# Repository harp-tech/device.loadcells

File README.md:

## Harp Load Cells Interface and Reader

This pair of boards can be used to acquire analog signals from load cells and output their data to a USB host. It is additionally able to emit programmable digital events.

### Key Features ###

* Load cells interface
  * Controls up to 2 load cells readers
  * Digital outputs can be regulated at 3V or 5V
* Load Cells Reader
  * Up to 4 load cell sensors
  * 1kHz sampling rate
  * Load cells offset compensation

### Connectivity ###

* Load cells interface
  * 1x BNC input signal (IN0)
  * 1x BNC output signal (Out0)
  * 1x screw terminal connector interface (GND, DOUT1 to DOUT8, DIN0)
  * 2x RJ45 for digital inputs (from load cells devices)
  * 1x stereo jack for clock sync input (CLKIN)
  * 1x USB (for computer)
  * 1x power barrel connector jack (12V only)
  * 1x screw terminal connector for 5V output (GND, +5V)
* Load Cells Reader
  * 4x flick lock connectors (X1 to X4) with 4 analog inputs each (5V, I+, I-, 0V)
  * 1x digital output [RJ45]

## Interface ##

The interface with the Harp board can be done through [Bonsai](https://bonsai-rx.org/) or a dedicated GUI (Graphical User Interface).

In order to use this GUI, there are some software that needs to be installed:

1 - Install the [drivers](https://bitbucket.org/fchampalimaud/downloads/downloads/UsbDriver-2.12.26.zip).

2 - Install the [runtime](https://bitbucket.org/fchampalimaud/downloads/downloads/Runtime-1.0.zip).

3 - Reboot the computer.

4 - Install the [GUI](https://bitbucket.org/fchampalimaud/downloads/downloads/Harp%20Load%20Cells%20v1.1.0.zip).

## Licensing ##

Each subdirectory will contain a license or, possibly, a set of licenses if it involves both hardware and software.

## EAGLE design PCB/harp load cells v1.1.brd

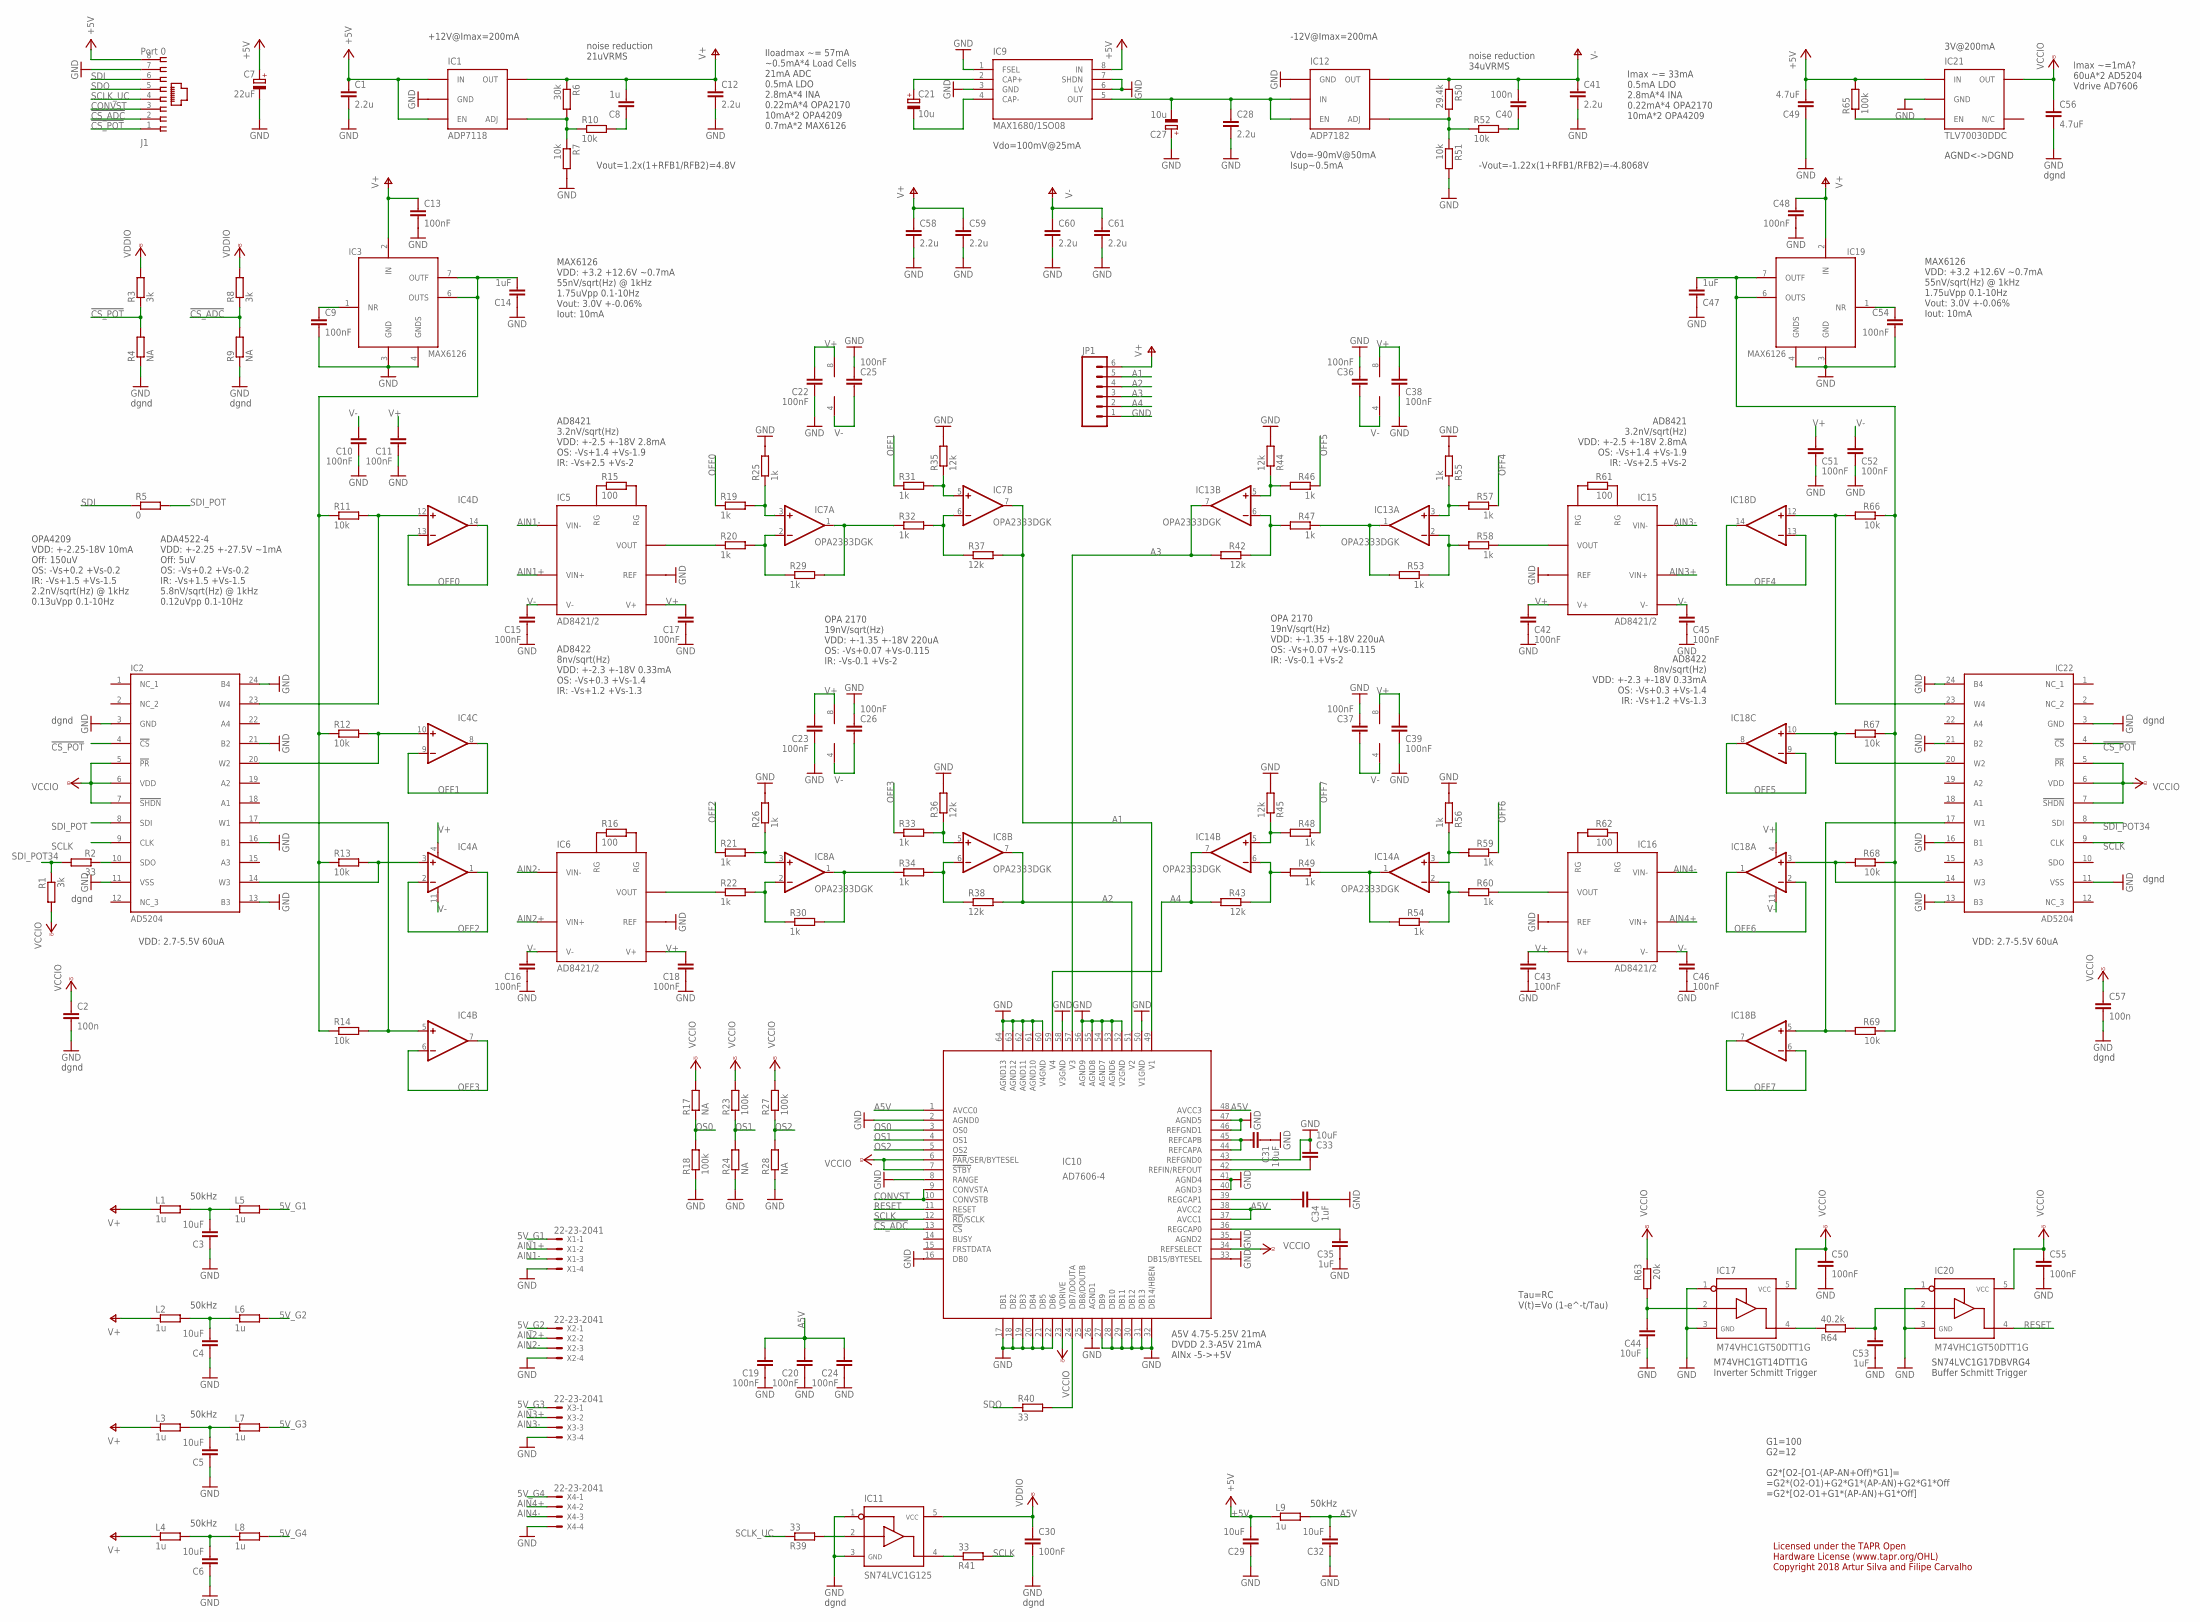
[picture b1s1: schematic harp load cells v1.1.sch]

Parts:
C1, C12, C28, C41, C58, C59, C60, C61: 2.2u; C0603
C2, C40, C57: 100n; C0402
C3, C4, C5, C6, C29, C31, C32, C33, C44: 10uF; C0603
C7: 22uF; CAP_100UF_HAND
C8: 1u; C0402
C9, C10, C11, C13, C15, C16, C17, C18, C19, C20, C22, C23, C24, C25, C26, C30, C36, C37, C38, C39, C42, C43, C45, C46, C48, C50, C51, C52, C54, C55: 100nF; C0402
C14, C47, C53: 1uF; C0603
C21, C27: 10u; A/3216-18W
C34, C35: 1uF; C0402
C49, C56: 4.7uF; C0603
IC1: ADP7118; TSOT23-5
IC2, IC22: AD5204; TSSOP-24
IC3, IC19: MAX6126; SO08
IC4, IC18: OPA4336T; TSSOP-14
IC5, IC6, IC15, IC16: AD8421/2; MSOP8
IC7, IC8, IC13, IC14: OPA2333DGK; MSOP08
IC9: MAX1680/1SO08; SO08
IC10: AD7606-4; LQFP-64
IC11: SN74LVC1G125; SOT23-5
IC12: ADP7182; TSOT23-5
IC17, IC20: M74VHC1GT50DTT1G; SOT23-5
IC21: TLV70030DDC; TSOT23-5
J1: Port 0; 520426-4
JP1: M06NO_SILK; 1X06_NO_SILK
L1, L2, L3, L4, L5, L6, L7, L8, L9: 1u; R0402
R1, R3, R8: 3k; R0402
R2, R39, R40, R41: 33; R0402
R4, R9, R17, R24, R28: NA; R0402
R5: 0; R0402
R6: 30k; R0402
R7, R10, R11, R12, R13, R14, R51, R52, R66, R67, R68, R69: 10k; R0402
R15, R16, R61, R62: 100; R0402
R18, R23, R27, R65: 100k; R0402
R19, R20, R21, R22, R25, R26, R29, R30, R31, R32, R33, R34, R46, R47, R48, R49, R53, R54, R55, R56, R57, R58, R59, R60: 1k; R0402
R35, R36, R37, R38, R42, R43, R44, R45: 12k; R0402
R50: 29.4k; R0402
R63: 20k; R0402
R64: 40.2k; R0402
X1, X2, X3, X4: 22-23-2041

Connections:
5V_G1: L5.2, X1.1
5V_G2: L6.2, X2.1
5V_G3: L7.2, X3.1
5V_G4: L8.2, X4.1
!CS_ADC: IC10.13 (!CS), J1.2, R8.1, R9.2
!CS_POT: IC2.4 (!CS), IC22.4 (!CS), J1.1, R3.1, R4.2
+5V: C1.1, C7.+, C29.2, C49.2, IC1.1 (IN), IC1.3 (EN), IC9.8 (IN), IC21.1 (IN), J1.8, L9.1, R65.2
A1: IC7.7 (OUT), IC10.49 (V1), JP1.5, R37.2
A2: IC8.7 (OUT), IC10.51 (V2), JP1.4, R38.2
A3: IC10.57 (V3), IC13.7 (OUT), JP1.3, R42.2
A4: IC10.59 (V4), IC14.7 (OUT), JP1.2, R43.2
A5V: C19.2, C20.2, C24.2, C32.2, IC10.1 (AVCC0), IC10.37 (AVCC1), IC10.38 (AVCC2), IC10.48 (AVCC3), L9.2
AIN1+: IC5.P$4 (VIN+), X1.2
AIN1-: IC5.P$1 (VIN-), X1.3
AIN2+: IC6.P$4 (VIN+), X2.2
AIN2-: IC6.P$1 (VIN-), X2.3
AIN3+: IC15.P$4 (VIN+), X3.2
AIN3-: IC15.P$1 (VIN-), X3.3
AIN4+: IC16.P$4 (VIN+), X4.2
AIN4-: IC16.P$1 (VIN-), X4.3
CONVST: IC10.9 (CONVSTA), IC10.10 (CONVSTB), J1.3
GND: C1.2, C2.2, C3.1, C4.1, C5.1, C6.1, C7.-, C9.2, C10.1, C11.1, C12.2, C13.2, C14.1, C15.1, C16.1, C17.1, C18.1, C19.1, C20.1, C22.1, C23.1, C24.1, C25.1, C26.1, C27.+, C28.2, C29.1, C30.2, C31.1, C32.1, C33.1, C34.1, C35.1, C36.1, C37.1, C38.1, C39.1, C41.2, C42.1, C43.1, C44.1, C45.1, C46.1, C47.1, C48.2, C49.1, C50.2, C51.1, C52.1, C53.1, C54.2, C55.2, C56.2, C57.2, C58.2, C59.2, C60.2, C61.2, IC1.2 (GND), IC2.3 (GND), IC2.11 (VSS), IC2.13 (B3), IC2.16 (B1), IC2.21 (B2), IC2.24 (B4), IC3.3 (GND), IC3.4 (GNDS), IC5.P$6 (REF), IC6.P$6 (REF), IC9.1 (FSEL), IC9.3 (GND), IC9.6 (LV), IC9.7 (SHDN), IC10.2 (AGND0), IC10.8 (RANGE), IC10.16 (DB0), IC10.17 (DB1), IC10.18 (DB2), IC10.19 (DB3), IC10.20 (DB4)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
unnamed: IC21.3 (EN), R65.1
unnamed: IC12.4 (ADJ), R50.2, R51.1, R52.1
unnamed: C44.2, IC17.2, R63.2
unnamed: C35.2, IC10.36 (REGCAP0)
unnamed: IC6.P$7 (VOUT), R22.1
unnamed: C40.1, R52.2
unnamed: C6.2, L4.2, L8.1
unnamed: IC17.4, R64.1
unnamed: C21.+, IC9.2 (CAP+)
unnamed: C21.-, IC9.4 (CAP-)
unnamed: C27.-, C28.1, IC9.5 (OUT), IC12.2 (IN), IC12.3 (EN)
unnamed: C53.2, IC20.2, R64.2
unnamed: IC7.6 (-IN), R32.2, R37.1
unnamed: C34.2, IC10.39 (REGCAP1)
unnamed: IC13.2 (-IN), R53.1, R58.2
unnamed: IC7.2 (-IN), R20.2, R29.1
unnamed: IC7.3 (+IN), R19.2, R25.1
unnamed: IC7.5 (+IN), R31.2, R35.1
unnamed: C33.2, IC10.42 (REFIN/REFOUT)
unnamed: IC13.3 (+IN), R55.1, R57.2
unnamed: IC13.6 (-IN), R42.1, R47.2
unnamed: IC13.5 (+IN), R44.1, R46.2
unnamed: C31.2, IC10.44 (REFCAPA), IC10.45 (REFCAPB)
unnamed: C8.1, R10.2
unnamed: IC1.4 (ADJ), R6.2, R7.1, R10.1
unnamed: IC5.P$2 (RG), R15.2
unnamed: IC5.P$3 (RG), R15.1
unnamed: IC5.P$7 (VOUT), R20.1
unnamed: IC8.2 (-IN), R22.2, R30.1
unnamed: IC6.P$2 (RG), R16.2
unnamed: IC6.P$3 (RG), R16.1
unnamed: IC8.3 (+IN), R21.2, R26.1
unnamed: IC7.1 (OUT), R29.2, R32.1
unnamed: IC8.6 (-IN), R34.2, R38.1
unnamed: C9.1, IC3.1 (NR)
unnamed: IC8.5 (+IN), R33.2, R36.1
unnamed: IC15.P$2 (RG), R61.2
unnamed: IC8.1 (OUT), R30.2, R34.1
unnamed: IC15.P$3 (RG), R61.1
unnamed: IC15.P$7 (VOUT), R58.1
unnamed: IC2.20 (W2), IC4.10 (+IN), R12.2
unnamed: IC16.P$2 (RG), R62.2
unnamed: IC2.17 (W1), IC4.5 (+IN), R14.2
unnamed: IC16.P$3 (RG), R62.1
unnamed: C14.2, IC3.6 (OUTS), IC3.7 (OUTF), R11.1, R12.1, R13.1, R14.1
unnamed: IC18.10 (+IN), IC22.20 (W2), R67.2
unnamed: IC18.12 (+IN), IC22.23 (W4), R66.2
unnamed: IC11.2, R39.2
unnamed: IC2.10 (SDO), R2.1
unnamed: C5.2, L3.2, L7.1
unnamed: IC18.3 (+IN), IC22.14 (W3), R68.2
unnamed: IC18.5 (+IN), IC22.17 (W1), R69.2
unnamed: IC13.1 (OUT), R47.1, R53.2
unnamed: C54.1, IC19.1 (NR)
unnamed: C47.2, IC19.6 (OUTS), IC19.7 (OUTF), R66.1, R67.1, R68.1, R69.1
unnamed: IC2.14 (W3), IC4.3 (+IN), R13.2
unnamed: IC14.2 (-IN), R54.1, R60.2
unnamed: IC14.3 (+IN), R56.1, R59.2
unnamed: IC14.6 (-IN), R43.1, R49.2
unnamed: IC14.5 (+IN), R45.1, R48.2
unnamed: IC2.23 (W4), IC4.12 (+IN), R11.2
unnamed: IC11.4, R41.1
unnamed: IC14.1 (OUT), R49.1, R54.2
unnamed: IC16.P$7 (VOUT), R60.1
unnamed: C4.2, L2.2, L6.1
unnamed: C3.2, L1.2, L5.1
unnamed: IC10.24 (DB7/DOUTA), R40.2
OFF0: IC4.13 (-IN), IC4.14 (OUT), R19.1
OFF1: IC4.8 (OUT), IC4.9 (-IN), R31.1
OFF2: IC4.1 (OUT), IC4.2 (-IN), R21.1
OFF3: IC4.6 (-IN), IC4.7 (OUT), R33.1
OFF4: IC18.13 (-IN), IC18.14 (OUT), R57.1
OFF5: IC18.8 (OUT), IC18.9 (-IN), R46.1
OFF6: IC18.1 (OUT), IC18.2 (-IN), R59.1
OFF7: IC18.6 (-IN), IC18.7 (OUT), R48.1
OS0: IC10.3 (OS0), R17.1, R18.2
OS1: IC10.4 (OS1), R23.1, R24.2
OS2: IC10.5 (OS2), R27.1, R28.2
RESET: IC10.11 (RESET), IC20.4
SCLK: IC2.9 (CLK), IC10.12 (!RD!/SCLK), IC22.9 (CLK), R41.2
SCLK_UC: J1.4, R39.1
SDI: J1.6, R5.1
SDI_POT: IC2.8 (SDI), R5.2
SDI_POT34: IC22.8 (SDI), R1.1, R2.2
SDO: J1.5, R40.1
V+: C8.2, C11.2, C12.1, C13.1, C17.2, C18.2, C22.2, C23.2, C38.2, C39.2, C42.2, C43.2, C48.1, C51.2, C58.1, C59.1, IC1.5 (OUT), IC3.2 (IN), IC4.4 (V+), IC5.P$8 (V+), IC6.P$8 (V+), IC7.8 (V+), IC8.8 (V+), IC13.8 (V+), IC14.8 (V+), IC15.P$8 (V+), IC16.P$8 (V+), IC18.4 (V+), IC19.2 (IN), JP1.6, L1.1, L2.1, L3.1, L4.1, R6.1
V-: C10.2, C15.2, C16.2, C25.2, C26.2, C36.2, C37.2, C40.2, C41.1, C45.2, C46.2, C52.2, C60.1, C61.1, IC4.11 (V-), IC5.P$5 (V-), IC6.P$5 (V-), IC7.4 (V-), IC8.4 (V-), IC12.5 (OUT), IC13.4 (V-), IC14.4 (V-), IC15.P$5 (V-), IC16.P$5 (V-), IC18.11 (V-), R50.1
VCCIO: C2.1, C30.1, C50.1, C55.1, C56.1, C57.1, IC2.5 (!PR), IC2.6 (VDD), IC2.7 (!SHDN), IC10.6 (!PAR!/SER/BYTESEL), IC10.7 (!STBY), IC10.23 (VDRIVE), IC10.34 (REFSELECT), IC11.5, IC17.5, IC20.5, IC21.5 (OUT), IC22.5 (!PR), IC22.6 (VDD), IC22.7 (!SHDN), R1.2, R3.2, R8.2, R17.2, R23.2, R27.2, R63.1

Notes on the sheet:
A5V 4.75-5.25V 21mA DVDD 2.3-A5V 21mA AINx -5->+5V
AD8421 3.2nV/sqrt(Hz) VDD: +-2.5 +-18V 2.8mA OS: -Vs+1.4 +Vs-1.9 IR: -Vs+2.5 +Vs-2
VDD: 2.7-5.5V 60uA
3V@200mA
50kHz
Licensed under the TAPR Open Hardware License (www.tapr.org/OHL) Copyright 2018 Artur Silva and Filipe Carvalho
Imax ~=1mA? 60uA*2 AD5204 Vdrive AD7606
AGND<->DGND
M74VHC1GT14DTT1G Inverter Schmitt Trigger
SN74LVC1G17DBVRG4 Buffer Schmitt Trigger
Tau=RC V(t)=Vo (1-e^-t/Tau)
dgnd
noise reduction 34uVRMS
-12V@Imax=200mA
-Vout=-1.22x(1+RFB1/RFB2)=-4.8068V
+12V@Imax=200mA
Vout=1.2x(1+RFB1/RFB2)=4.8V
noise reduction 21uVRMS
OPA4209 VDD: +-2.25-18V 10mA Off: 150uV OS: -Vs+0.2 +Vs-0.2 IR: -Vs+1.5 +Vs-1.5 2.2nV/sqrt(Hz) @ 1kHz 0.13uVpp 0.1-10Hz
Vdo=100mV@25mA
Vdo=-90mV@50mA Isup~0.5mA
AD8422 8nv/sqrt(Hz) VDD: +-2.3 +-18V 0.33mA OS: -Vs+0.3 +Vs-1.4 IR: -Vs+1.2 +Vs-1.3
Imax ~= 33mA 0.5mA LDO 2.8mA*4 INA 0.22mA*4 OPA2170 10mA*2 OPA4209
OPA 2170 19nV/sqrt(Hz) VDD: +-1.35 +-18V 220uA OS: -Vs+0.07 +Vs-0.115 IR: -Vs-0.1 +Vs-2
ADA4522-4 VDD: +-2.25 +-27.5V ~1mA Off: 5uV OS: -Vs+0.2 +Vs-0.2 IR: -Vs+1.5 +Vs-1.5 5.8nV/sqrt(Hz) @ 1kHz 0.12uVpp 0.1-10Hz
MAX6126 VDD: +3.2 +12.6V ~0.7mA 55nV/sqrt(Hz) @ 1kHz 1.75uVpp 0.1-10Hz Vout: 3.0V +-0.06% Iout: 10mA
Iloadmax ~= 57mA ~0.5mA*4 Load Cells 21mA ADC 0.5mA LDO 2.8mA*4 INA 0.22mA*4 OPA2170 10mA*2 OPA4209 0.7mA*2 MAX6126
G1=100 G2=12 G2*[O2-[O1-(AP-AN+Off)*G1]= =G2*(O2-O1)+G2*G1*(AP-AN)+G2*G1*Off =G2*[O2-O1+G1*(AP-AN)+G1*Off]

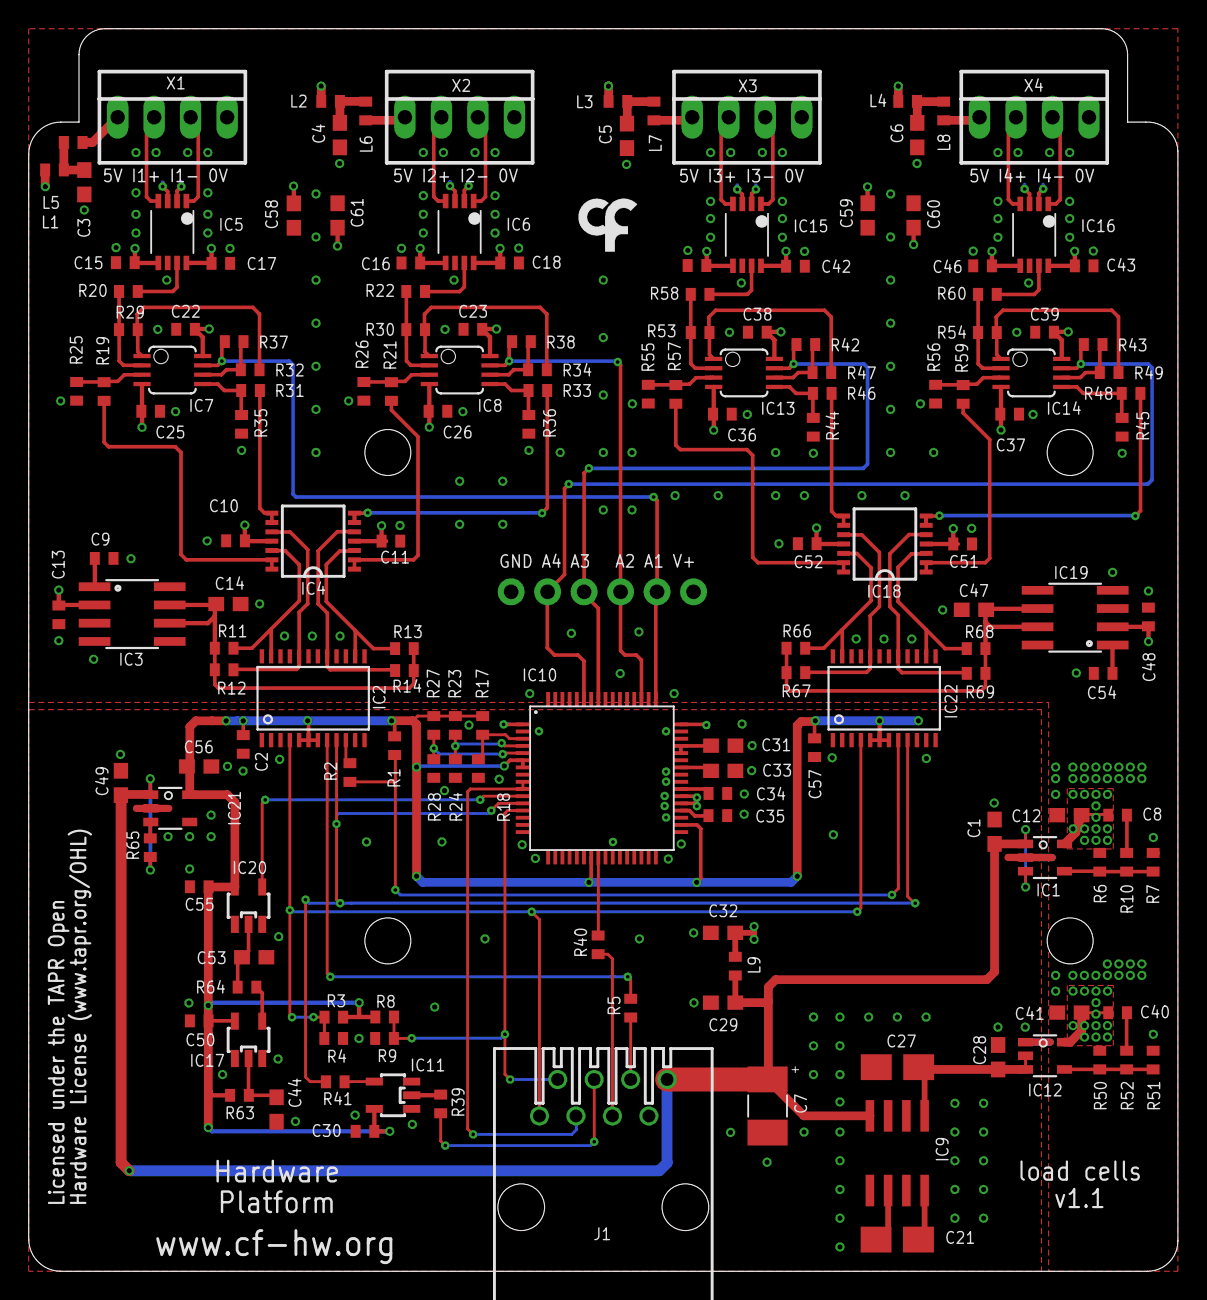
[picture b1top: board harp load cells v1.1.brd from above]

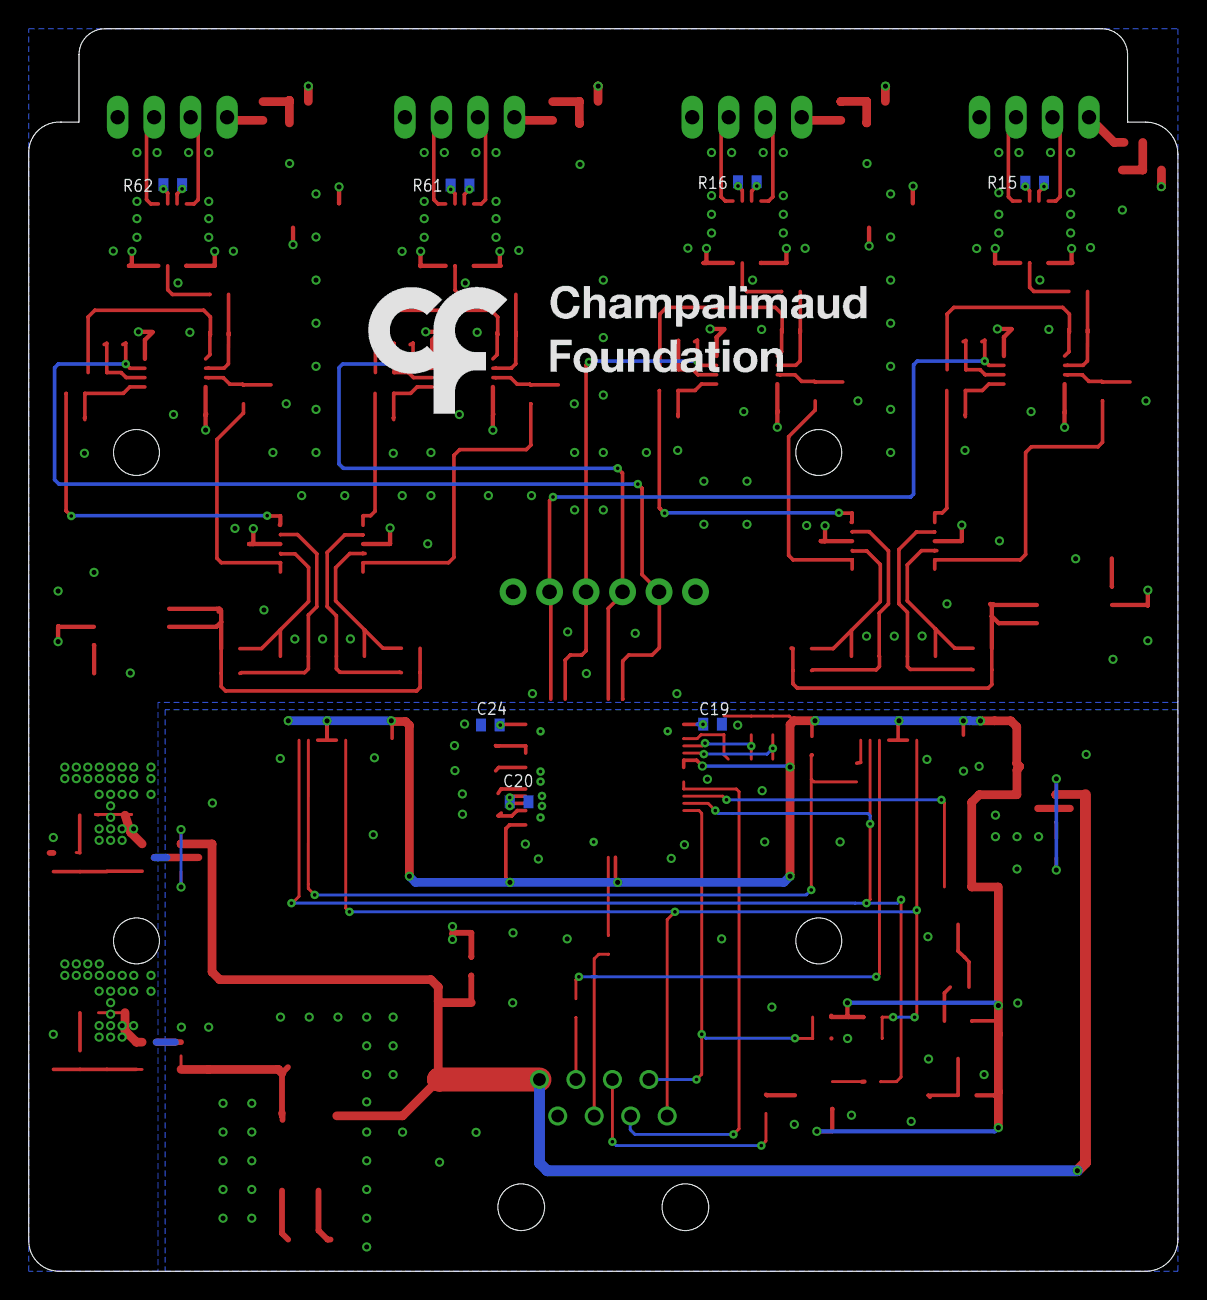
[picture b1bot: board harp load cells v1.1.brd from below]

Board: 4 copper layers, 80.0 x 86.5 mm, 169 parts (8 on the bottom side), 110 nets.

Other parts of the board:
U$1: LOGO_5
U$4: LOGO_7

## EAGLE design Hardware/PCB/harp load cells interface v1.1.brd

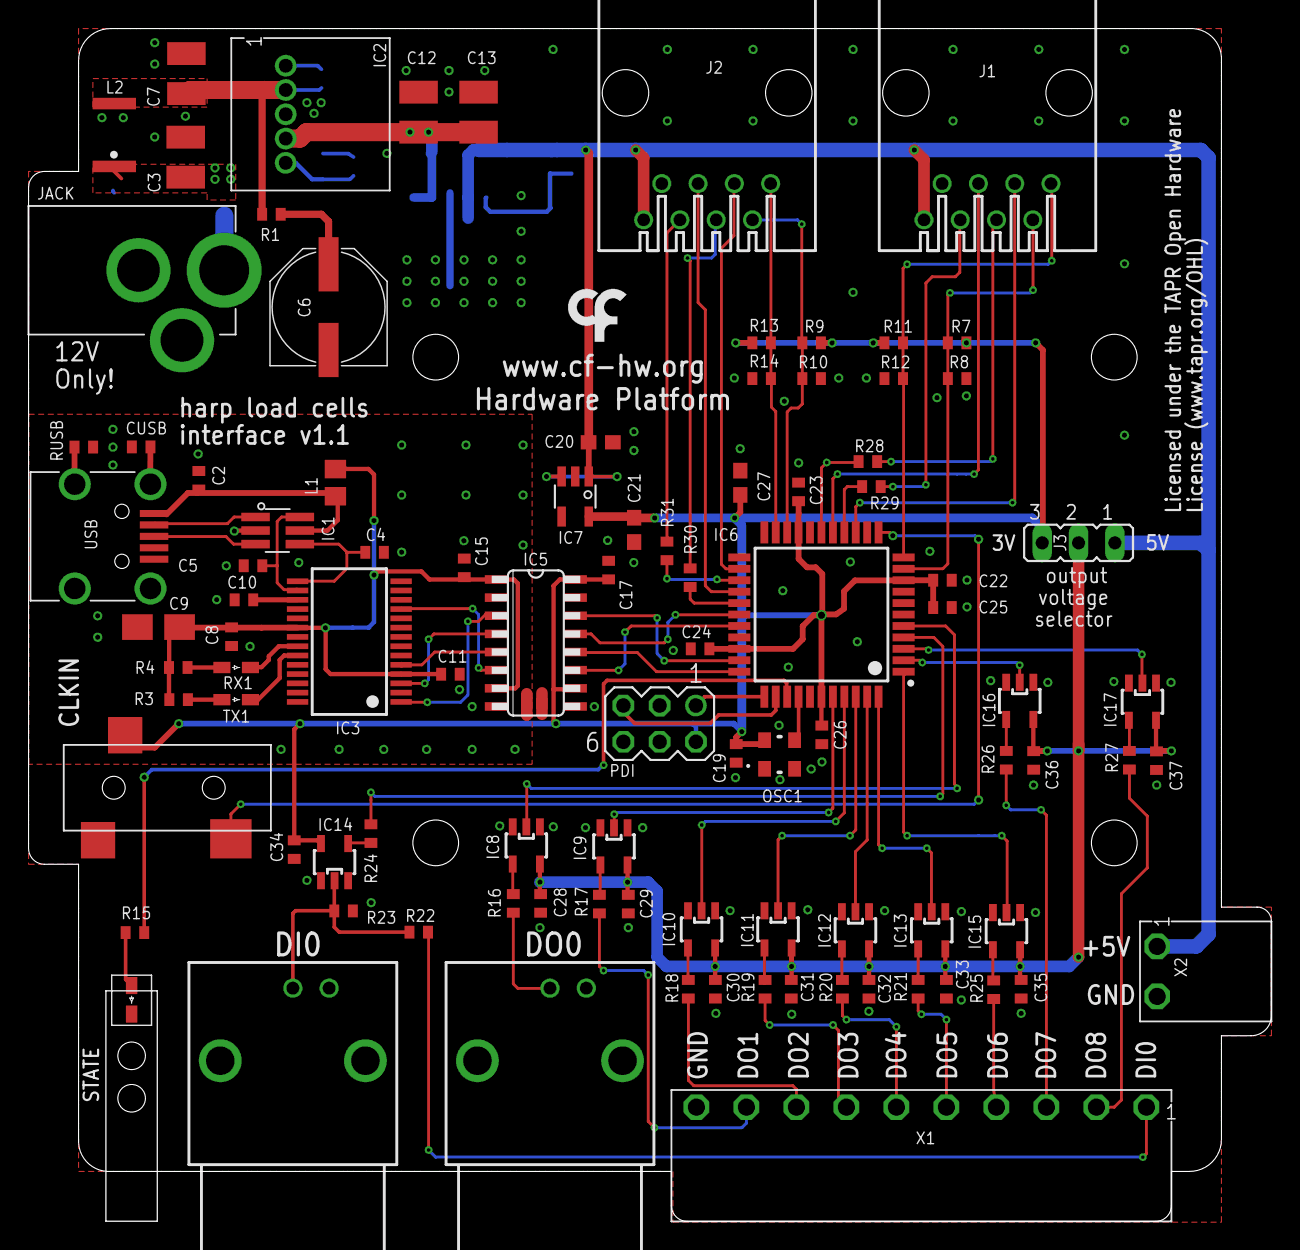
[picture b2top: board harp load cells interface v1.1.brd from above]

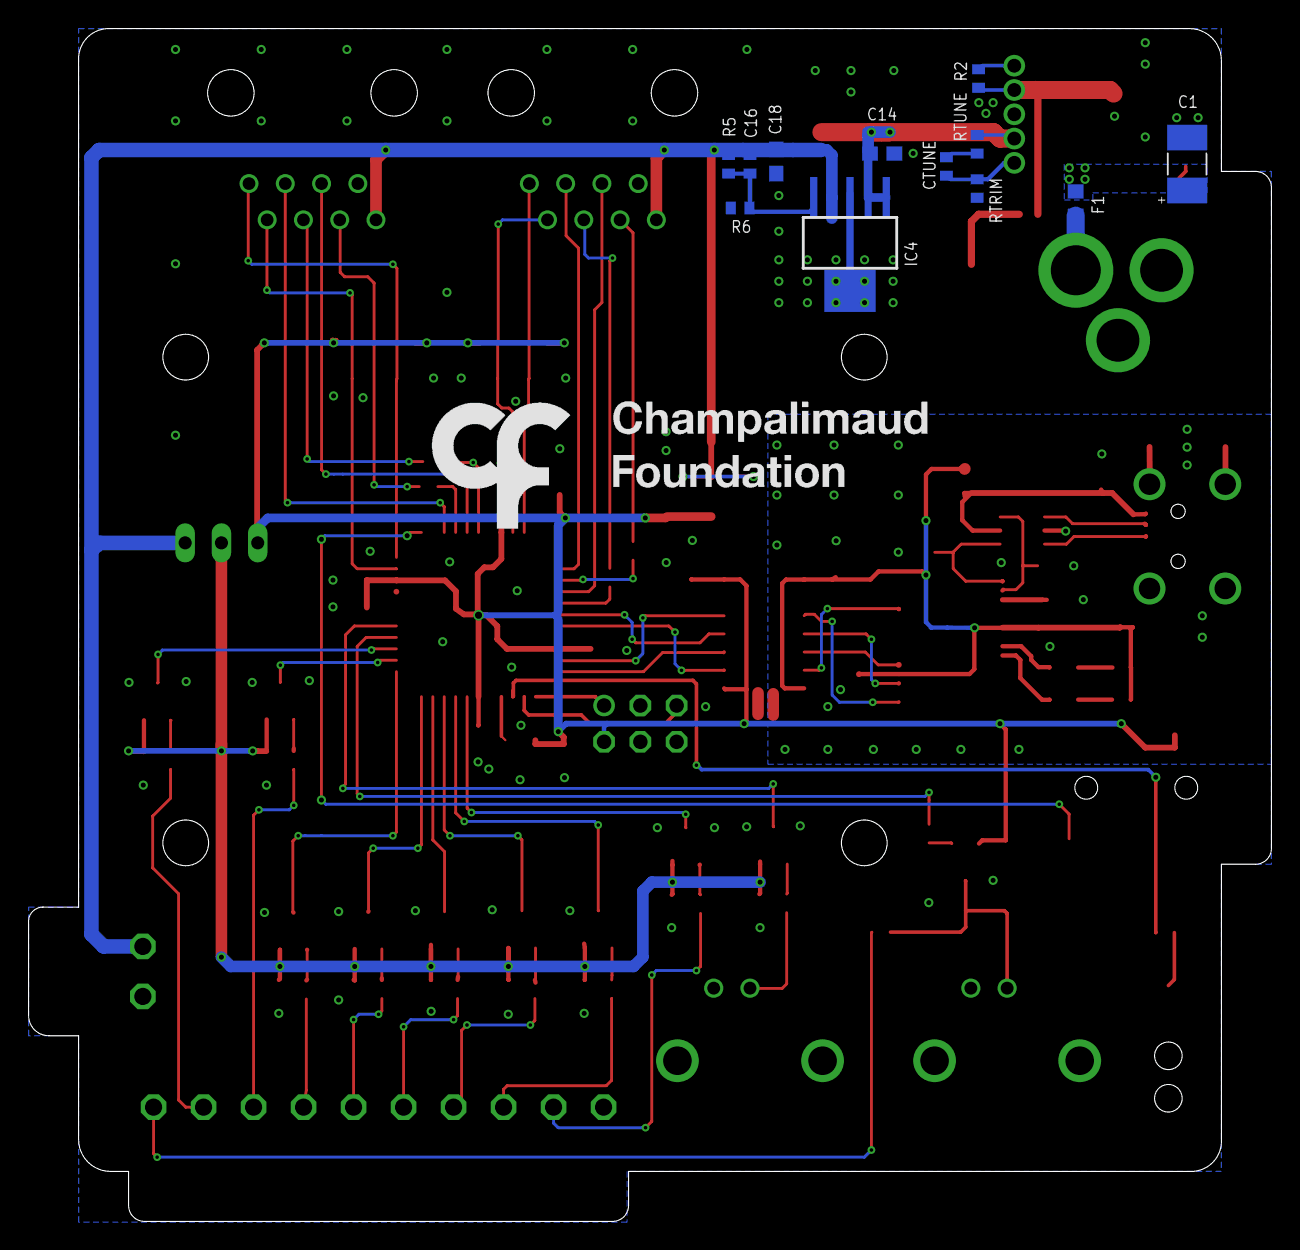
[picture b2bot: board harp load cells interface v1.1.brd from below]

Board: 2 copper layers, 87.0 x 83.5 mm, 113 parts (13 on the bottom side), 88 nets.

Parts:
C1: 22uF; CAP_100UF_HAND
C2, C8, C10, C11, C15, C17, C19, C22, C23, C24, C28, C29, C30, C31, C32, C33, C34, C35, C36, C37: 100nF; C0402
C3, C7: 22uF; C1210
C4, C5: 47pF; C0402
C6: 100uF; PANASONIC_E
C9: 4.7uF; A/3216-18W
C12, C13: 47uF; C1210
C14, C18, C20, C21, C27: 10uF; C0603
C16: 13pF; C0402
C25, C26: 330nF; C0402
CLKIN: 35RASMT2BHNTRX
CTUNE: NA; C0402
CUSB: 4.7nF; C0402
F1: 1A FB; R0603
IC1: USBLC6-2SC6; SOT23-6L
IC2: DC-DC-SIP-5; SIP-5
IC3: FT232RL; SSOP28
IC4: TPS78630DCQ; SOT223-6
IC5: SI8642BC-B-IS1; NSOIC-16
IC6: ATXMEGA128A4U-AU; QFP80P1200X1200X120-44N
IC7: LP5907MFX-3.3; TSOT23-5
IC8, IC9, IC10, IC11, IC12, IC13, IC14, IC15, IC16, IC17: SN74LVC1G125; SOT23-5
IN0: BNC; BNC_RA
J1, J2: Port 0; 520426-4
J3: JP2
JACK: DC_JACK2.1MM; DC_POWER_INPUT_2.1MM
L1: ???; R0805
L2: 1.5u; IND_LPS4012
OSC1: OSCILLATOR_3.2X2.5
OUT0: BNC; BNC_RA
PDI: MA03-2
R1: 0; R0402
R2, R7, R9, R11, R13: NA; R0402
R3: 2050 NA; R0402
R4: 680 NA; R0402
R5: 95.3k; R0402
R6: 30.9k; R0402
R8, R10, R12, R14, R23: 100k; R0402
R15: 68; R0402
R16, R17, R18, R19, R20, R21, R24, R25, R26, R27, R28, R29, R30, R31: 33; R0402
R22: 330; R0402
RTRIM: 243; R0402
RTUNE: NA; R0402
RUSB: 1M; R0402
RX1: GREEN NA; LED_HAND
STATE: GREEN; LED_HAND
TP1, TP2: TPTP08SQ; TP08SQ
TX1: RED NA; LED_HAND
U$1: LED_PIPE_7513D2-L
U$2: LOGO_5
U$4: LOGO_7
USB: 240-0002-1
X1: CON_3.5MM_1X10
X2: CON_3.5MM_1X2

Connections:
3V3OUT: C10.1, IC3.17
!CS0_0: IC6.14, J1.3
!CS0_1: IC6.10, J1.2, R7.1, R8.2
!CS0_2: IC6.11, J1.1, R11.1, R12.2
!CS1_0: IC6.24, J2.3
!CS1_1: IC6.20, J2.2, R9.1, R10.2
!CS1_2: IC6.21, J2.1, R13.1, R14.2
+5V: C16.1, C18.1, C20.1, IC4.P$4, IC7.1, IC7.3, J1.8, J2.8, J3.1, R5.2, X2.P1
+12V: C1.+, C3.1, F1.1, L2.1
+V: C28.1, C29.1, C30.1, C31.1, C32.1, C33.1, C35.1, C36.1, C37.1, IC8.5, IC9.5, IC10.5, IC11.5, IC12.5, IC13.5, IC15.5, IC16.5, IC17.5, J3.2
BNC_DI0: IC14.2, IN0.1, R22.2, R23.2
CLK_SYNC: CLKIN.4, IC6.12
CTS: IC5.11, IC6.29
DCIN: C7.1, IC2.P2, L2.2, R1.2, R2.2
DI0: R22.1, X1.P1
DO0: OUT0.1, R16.2
DO1: R17.2, X1.P9
DO2: R18.2, X1.P8
DO3: R19.2, X1.P7
DO4: R20.2, X1.P6
DO5: R21.2, X1.P5
DO6: R25.2, X1.P4
DO7: R26.2, X1.P3
DO8: R27.2, X1.P2
FT_CTS: IC3.11, IC5.6
FT_RTS: IC3.3, IC5.4
FT_RXD: IC3.5, IC5.5
FT_TXD: IC3.1, IC5.3
GND: C1.-, C3.2, C6.-, C7.2, C12.2, C13.2, C14.2, C17.2, C18.2, C19.2, C20.2, C21.2, C22.2, C23.2, C24.2, C25.2, C26.2, C27.2, C28.2, C29.2, C30.2, C31.2, C32.2, C33.2, C34.2, C35.2, C36.2, C37.2, CLKIN.5, IC2.P3, IC4.P$3, IC4.P$6, IC5.9, IC5.15, IC6.8, IC6.18, IC6.30, IC6.38, IC7.2, IC8.1, IC8.3, IC9.1, IC9.3, IC10.1, IC10.3, IC11.1, IC11.3, IC12.1, IC12.3, IC13.1, IC13.3, IC14.1, IC14.3, IC15.1, IC15.3, IC16.1, IC16.3, IC17.1, IC17.3, IN0.2, J1.7, J2.7, JACK.P2, JACK.P3, OSC1.P$2, OUT0.2, PDI.6, R6.1, R8.1, R10.1, R12.1, R14.1, R23.1, RTRIM.1, STATE.K, TP2.TP, X1.P10, X2.P2
GND2: C2.2, C4.2, C5.2, C8.2, C9.-, C10.2, C11.2, C15.2, CUSB.2, IC1.P$2, IC3.7, IC3.18, IC3.21, IC3.25, IC3.26, IC5.2, IC5.8, RUSB.2, TP1.TP, USB.P$5
IN00: IC6.4, R24.2
MISO0: IC6.16, J1.5
MISO1: IC6.26, J2.5
MOSI0: IC6.15, R29.1
MOSI0_T: J1.6, R29.2
MOSI1: IC6.25, R31.2
MOSI1_T: J2.6, R31.1
unnamed: IC16.4, R26.1
unnamed: IC15.4, R25.1
unnamed: IC10.4, R18.1
unnamed: R4.1, RX1.A
unnamed: IC17.4, R27.1
unnamed: IC3.22, RX1.K
unnamed: IC9.4, R17.1
unnamed: IC12.4, R20.1
unnamed: IC8.4, R16.1
unnamed: CTUNE.2, IC2.P5, RTRIM.2
unnamed: IC1.P$3, USB.P$3
unnamed: CTUNE.1, RTUNE.1
unnamed: CUSB.1, USB.SHIELD_4
unnamed: IC2.P1, R2.1
unnamed: IC13.4, R21.1
unnamed: F1.2, JACK.P1
unnamed: IC11.4, R19.1
unnamed: C16.2, IC4.P$5, R5.1, R6.2
unnamed: IC14.4, R24.1
unnamed: R15.1, STATE.A
unnamed: C6.+, R1.1
unnamed: C2.1, IC1.P$5, L1.2, USB.P$1
unnamed: R3.1, TX1.A
unnamed: IC3.23, TX1.K
unnamed: RUSB.1, USB.SHIELD_1
unnamed: IC1.P$1, USB.P$2
OSC1: IC6.37, OSC1.P$3
OUT00: IC6.5, IC8.2
OUT01: IC6.40, IC9.2
OUT02: IC6.41, IC10.2
OUT03: IC6.42, IC11.2
OUT04: IC6.43, IC12.2
OUT05: IC6.44, IC13.2
OUT06: IC6.1, IC15.2
OUT07: IC6.2, IC16.2
OUT08: IC6.3, IC17.2
P5.45V: C12.1, C13.1, C14.1, IC2.P4, IC4.P$1, IC4.P$2, RTUNE.2
PDI-CLK: IC6.35, PDI.5
PDI-DATA: IC6.34, PDI.1
RTS: IC5.13, IC6.28
RXD: IC5.12, IC6.33
SCK0: IC6.17, R28.1
SCK0_T: J1.4, R28.2
SCK1: IC6.27, R30.2
SCK1_T: J2.4, R30.1
STATE: IC6.36, R15.2
TXD: IC5.14, IC6.32
USB5V: C8.1, C9.+, C11.1, C15.1, IC3.4, IC3.20, IC5.1, IC5.7, L1.1, R3.2, R4.2
USBDM: C5.1, IC1.P$6, IC3.16
USBDP: C4.1, IC1.P$4, IC3.15
VCCIO: C17.1, C19.1, C21.1, C22.1, C23.1, C24.1, C25.1, C26.1, C27.1, C34.1, CLKIN.1, IC5.10, IC5.16, IC6.9, IC6.19, IC6.31, IC6.39, IC7.5, IC14.5, J3.3, OSC1.P$4, PDI.2, R7.2, R9.2, R11.2, R13.2

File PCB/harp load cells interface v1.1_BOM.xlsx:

| Part(s) | Quantity | Description | Distributor | Part. No.
 | IC1 | 1 | ESD Protection Low Cap | Mouser | 511-USBLC6-2SC6Y
 | IC2 | 1 | Conversores CC/CC sem isolação 12Vin, 0.591-6Vout 1.5A, Positive Logic | Mouser | 580-OKR-T/1.5-W12-C
 | IC3 | 1 | IC USB USB to Serial UART Enhanced IC SSOP-28 | Mouser | 895-FT232RL
 | IC4 | 1 | Reguladores de tensão de LDO High PSRR Fast RF High-Enable 1.5A | Mouser | 595-TPS78601DCQR
 | IC5 | 1 | Isoladores digitais Quad Ch 3.75V Iso 150M 2/2 NB, DO=LO | Mouser | 634-SI8642BC-B-IS1
 | IC6 | 1 | Microcontroladores de 8 bits - MCU 44TQFP, IND TEMP GREEN, 1.6-3.6V | Mouser | 556-ATXMEGA128A4U-AU
 | IC7 | 1 | LDO 250mA Ultra-Lo Noise LDO Reg | Mouser | 595-LP5907MFX-3.3NPB
 | IC8, IC9, IC10, IC11, IC12, IC13, IC14, IC15, IC16, IC17 | 10 | M74VHC1GT50DTT1G Buffer, Non-Inverting, 1.65V to 5.5V, SOT-23-5 | Mouser | 863-M74VHC1GT50DTT1G
 | C16 | 1 | CAP CER 13pF 50V ±5% C0G 0402 | Mouser | 81-GRM1555C1H130JA1D
 | C4, C5 | 2 | CAP CER 47pF 50V ±5% C0G 0402 | Mouser | 77-VJ0402A470JXACBC
 | CUSB | 1 | CAP CER 4.7nF 100V ±10% X7R 0402 | Mouser | 81-GRM155R72A472KA01
 | C2, C8, C10, C11, C15, C17, C19, C22, C23, C24, C25, C28, C29, C30, C31, C32, C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 | 21 | CAP CER 100nF 10V X5R 0402 | REEL | REEL
 | C26 | 1 | CAP CER 0.33uF 10V ±10% X5R 0402 | Mouser | GRM155R61A334KE15D
 | C9 | 1 | CAP TAN 4.7uF 6.3V ±10% 1206 | Mouser | 80-T491A475K006
 | C14, C18, C20, C21, C27 | 5 | CAP CER 10uF 10V ±10% X5R 0603 | Mouser | 81-GRM188R61A106KE9D
 | C1 | 1 | CAP TAN 22uF 20V ±10% 1210 | Mouser | 667-20TQC22MYFB
 | C3, C7 | 2 | CAP CER 22uF 25V ±10% X5R 1210 | Mouser | 81-GRM32ER61E226KE15
 | C12, C13 | 2 | CAP CER 47uF 10V ±10% X5R 1210 | Mouser | 81-GRM32ER61A476KE20
 | C6 | 1 | CAP ELE 100uF 25V ±20% | Mouser | 667-EEE-FK1E101P
 | R1 | 1 | RES SMD 0Ω OHM 5% 0402 | Mouser | 667-ERJ-2GE0R00X
 | R16, R17, R18, R19, R20, R21, R24, R25, R26, R27, R28, R29, R30, R31 | 14 | RES SMD 0402 33Ω, ± 1% | Mouser | 71-CRCW0402-33-E3
 | R15 | 1 | RES SMD 68Ω OHM 5% 0402 | Mouser | 71-CRCW0402-68-E3
 | RTRIM | 1 | RES SMD 243Ω OHM 1% 0402 | Mouser | 667-ERJ-2RKF2430X
 | R22 | 1 | RES SMD 330Ω OHM 1% 0402 | Mouser | 667-ERJ-PA2F3300X
 | R6 | 1 | RES SMD 30.9kΩ 1% 0402 | Mouser | 71-CRCW0402-30.9K-E3
 | R5 | 1 | RES SMD 95.3kΩ 1% 0402 | Mouser | 667-ERJ-2RKF9532X
 | R8, R10, R12, R14, R23 | 5 | RES SMD 100kΩ 1% 0402 | REEL | REEL
 | RUSB | 1 | RES SMD 1MΩ 1% 0402 | Mouser | 652-CR0402FX-1004GLF
 | F1 | 0 | 0603SFS100F/32-2 - Fuse, Surface Mount, 0603SFS Series, 1 A, 32 VDC, Slow Blow,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 | Mouser | 650-0603SFS100F/32-2
 | STATE | 1 | LED, Green, 1.6mm x 0.8mm, 566 nm, 2.1 V, 20 mA, 15 mcd | Mouser | 78-TLMP1100-GS08
 | OSC1 | 1 | 32MHz 10ppm | Mouser | 998-1001CI5032.0000T
 | CLKIN | 1 | SMT 3.5 STEREO REEL | Mouser | 502-35RASMT2BHNTRX
 | L2 | 1 | Indutores fixos LPS4012 Low Profile 1.5uH 2.2A 20% SMD | Mouser | 994-LPS4012-152MRB
 | L1 | 1 | 40ohms 100MHz 1.5A Monolithic 0805 SMD | Mouser | 875-MI0805K400R-10
 | PDI | 1 | 6P DR UNSHRD HRD | Mouser | 649-67996-206HLF
 | J1, J2 | 2 | Conectores modulares/Conectores de Ethernet 8/8 R/A MOD JACK | Mouser | 571-2158771
 |  | 2 | Ethernet Cable, Patch Lead, Cat5e, RJ45 Plug to RJ45 Plug, Beige, 500 mm | Farnell | 1526101
 | USB | 1 | UX60-MB-5S8 | Mouser | 798-UX60-MB-5S8
 | USB Cable | 1 | USB A - MINI-B 1M BLACK | Mouser | 538-88732-8602
 |  | 1 | Tubos de Luz LED CML LIGHTPIPE | Mouser | 606-7513D2-L
 | JACK | 1 | CC PCB 2.1MM | Mouser | 163-179PH-EX
 | WALL ADAPTER | 1 | AC/DC Power Supply, Class II, Fixed, 1 Output, 90 V, 264 V, 12 W, 12 V | Farnell | VEL12US120-EU-JA
 | J1 | 1 | C-Grid III 90120 Series, Through Hole, Header, 3 Contacts, 2.54 mm | Mouser | 538-90120-0763
 | Jumper | 1 | Jumper (Busbar), Shunt, PCB Connectors, 2, 2.54 mm | Farnell | 4218176
 | IN0, OUT0 | 2 | CONN BNC JACK R/A 50 OHM | Mouser | 571-5227161-1
 |  | 1 | 20.1550M/2-E - Pluggable Terminal Block, 3.5 mm, 2 Ways, 28 AWG, 16 AWG, 1.5 mm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 | Farnell | 2575215
 |  | 1 | 20.1550M/10-E - Pluggable Terminal Block, 3.5 mm, 10 Ways, 28 AWG, 16 AWG, 1.5 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 | Farnell | 2575213
 | X2 | 1 | 20.155MH/2-E - Terminal Block, Header, 3.5 mm, 2 Ways, 10 A, 250 V, Through Hol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 | Farnell | 2517858
 | X1 | 1 | 20.155MH/10-E - Terminal Block, Header, 3.5 mm, 10 Ways, 10 A, 250 V, Through H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 | Farnell | 2575221
 |  | 8 | 1110030 - Nut, Hex, M3, Nylon 6.6, Pack of 50 | Farnell | 1110030
 |  | 4 | Machine Screw, M3, 10 mm, Nylon (Polyamide), Pan Head Slotted, PK25 | Farnell | 1514410
 | Components | 116
 | Licensed under the TAPR Open Hardware License (www.tapr.org/OHL)
 | Copyright 2018 Artur Silva and Filipe Carvalho

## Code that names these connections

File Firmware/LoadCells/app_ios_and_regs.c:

#include <avr/io.h>
#include "hwbp_core_types.h"
#include "app_ios_and_regs.h"

/************************************************************************/
/* Configure and initialize IOs                                         */
/************************************************************************/
void init_ios(void)
{	/* Configure input pins */
	io_pin2in(&PORTB, 0, PULL_IO_UP, SENSE_IO_EDGES_BOTH);               // DI0
	io_pin2in(&PORTC, 6, PULL_IO_UP, SENSE_IO_EDGES_BOTH);               // MISO0
	io_pin2in(&PORTD, 6, PULL_IO_UP, SENSE_IO_EDGES_BOTH);               // MISO1

	/* Configure input interrupts */
	io_set_int(&PORTB, INT_LEVEL_LOW, 0, (1<<0), false);                 // DI0

	/* Configure output pins */
	io_pin2out(&PORTB, 1, OUT_IO_DIGITAL, IN_EN_IO_EN);                  // DO0
	io_pin2out(&PORTA, 0, OUT_IO_DIGITAL, IN_EN_IO_EN);                  // DO1
	io_pin2out(&PORTA, 1, OUT_IO_DIGITAL, IN_EN_IO_EN);                  // DO2
	io_pin2out(&PORTA, 2, OUT_IO_DIGITAL, IN_EN_IO_EN);                  // DO3
	io_pin2out(&PORTA, 3, OUT_IO_DIGITAL, IN_EN_IO_EN);                  // DO4
	io_pin2out(&PORTA, 4, OUT_IO_DIGITAL, IN_EN_IO_EN);                  // DO5
	io_pin2out(&PORTA, 5, OUT_IO_DIGITAL, IN_EN_IO_EN);                  // DO6
	io_pin2out(&PORTA, 6, OUT_IO_DIGITAL, IN_EN_IO_EN);                  // DO7
	io_pin2out(&PORTA, 7, OUT_IO_DIGITAL, IN_EN_IO_EN);                  // DO8
	io_pin2out(&PORTC, 1, OUT_IO_WIREDAND, IN_EN_IO_EN);                 // CS0_2
	io_pin2out(&PORTC, 0, OUT_IO_WIREDAND, IN_EN_IO_EN);                 // CS0_1
	io_pin2out(&PORTC, 4, OUT_IO_DIGITAL, IN_EN_IO_EN);                  // CS0_0
	io_pin2out(&PORTC, 5, OUT_IO_DIGITAL, IN_EN_IO_DIS);                 // MOSI0
	io_pin2out(&PORTC, 7, OUT_IO_DIGITAL, IN_EN_IO_DIS);                 // SCK0
	io_pin2out(&PORTD, 1, OUT_IO_WIREDAND, IN_EN_IO_EN);                 // CS1_2
	io_pin2out(&PORTD, 0, OUT_IO_WIREDAND, IN_EN_IO_EN);                 // CS1_1
	io_pin2out(&PORTD, 4, OUT_IO_DIGITAL, IN_EN_IO_EN);                  // CS1_0
	io_pin2out(&PORTD, 5, OUT_IO_DIGITAL, IN_EN_IO_DIS);                 // MOSI1
	io_pin2out(&PORTD, 7, OUT_IO_DIGITAL, IN_EN_IO_DIS);                 // SCK1

	/* Initialize output pins */
	clr_DO0;
	clr_DO1;
	clr_DO2;
	clr_DO3;
	clr_DO4;
	clr_DO5;
	clr_DO6;
	clr_DO7;
	clr_DO8;
	set_CS0_2;
	set_CS0_1;
	set_CS0_0;
	clr_MOSI0;
	clr_SCK0;
	set_CS1_2;
	set_CS1_1;
	set_CS1_0;
	clr_MOSI1;
	clr_SCK1;
}

/************************************************************************/
/* Registers' stuff                                                     */
/************************************************************************/
AppRegs app_regs;

uint8_t app_regs_type[] = {
	TYPE_U8,
	TYPE_I16,
	TYPE_U8,
	TYPE_U8,
	TYPE_U8,
	TYPE_U8,
	TYPE_U8,
	TYPE_U8,
	TYPE_U8,
	TYPE_U8,
	TYPE_U16,
	TYPE_U16,
	TYPE_U16,
	TYPE_U16,
	TYPE_U8,
	TYPE_U8,
	TYPE_I16,
	TYPE_I16,
	TYPE_I16,
	TYPE_I16,
	TYPE_I16,
	TYPE_I16,
	TYPE_I16,
	TYPE_I16,
	TYPE_U8,
	TYPE_U8,
	TYPE_U8,
	TYPE_U8,
	TYPE_U8,
	TYPE_U8,
	TYPE_U8,
	TYPE_U8,
	TYPE_U8,
	TYPE_U8,
	TYPE_I16,
	TYPE_I16,
	TYPE_I16,
	TYPE_I16,
	TYPE_I16,
	TYPE_I16,
	TYPE_I16,
	TYPE_I16,
	TYPE_U16,
	TYPE_U16,
	TYPE_U16,
	TYPE_U16,
	TYPE_U16,
	TYPE_U16,
	TYPE_U16,
	TYPE_U16,
	TYPE_U16,
	TYPE_U16,
	TYPE_U16,
	TYPE_U16,
	TYPE_U16,
	TYPE_U16,
	TYPE_U16,
	TYPE_U16,
	TYPE_U8
};

uint16_t app_regs_n_elements[] = {
	1,
	8,
	1,
	1,
	1,
	1,
	1,
	1,
	1,
	1,
	1,
	1,
	1,
	1,
	1,
	1,
	1,
	1,
	1,
	1,
	1,
	1,
	1,
	1,
	1,
	1,
	1,
	1,
	1,
	1,
	1,
	1,
	1,
	1,
	1,
	1,
	1,
	1,
	1,
	1,
	1,
	1,
	1,
	1,
	1,
	1,
	1,
	1,
	1,
	1,
	1,
	1,
	1,
	1,
	1,
	1,
	1,
	1,
	1
};

uint8_t *app_regs_pointer[] = {
	(uint8_t*)(&app_regs.REG_START),
	(uint8_t*)(app_regs.REG_LOAD_CELLS),
	(uint8_t*)(&app_regs.REG_DI0),
	(uint8_t*)(&app_regs.REG_DO0),
	(uint8_t*)(&app_regs.REG_THRESHOLDS),
	(uint8_t*)(&app_regs.REG_RESERVED0),
	(uint8_t*)(&app_regs.REG_RESERVED1),
	(uint8_t*)(&app_regs.REG_DI0_CONF),
	(uint8_t*)(&app_regs.REG_DO0_CONF),
	(uint8_t*)(&app_regs.REG_DO0_PULSE),
	(uint8_t*)(&app_regs.REG_DO_SET),
	(uint8_t*)(&app_regs.REG_DO_CLEAR),
	(uint8_t*)(&app_regs.REG_DO_TOGGLE),
	(uint8_t*)(&app_regs.REG_DO_OUT),
	(uint8_t*)(&app_regs.REG_RESERVED2),
	(uint8_t*)(&app_regs.REG_RESERVED3),
	(uint8_t*)(&app_regs.REG_OFFSET_CH0),
	(uint8_t*)(&app_regs.REG_OFFSET_CH1),
	(uint8_t*)(&app_regs.REG_OFFSET_CH2),
	(uint8_t*)(&app_regs.REG_OFFSET_CH3),
	(uint8_t*)(&app_regs.REG_OFFSET_CH4),
	(uint8_t*)(&app_regs.REG_OFFSET_CH5),
	(uint8_t*)(&app_regs.REG_OFFSET_CH6),
	(uint8_t*)(&app_regs.REG_OFFSET_CH7),
	(uint8_t*)(&app_regs.REG_RESERVED4),
	(uint8_t*)(&app_regs.REG_DOS_TH_INV),
	(uint8_t*)(&app_regs.REG_DO0_CH),
	(uint8_t*)(&app_regs.REG_DO1_CH),
	(uint8_t*)(&app_regs.REG_DO2_CH),
	(uint8_t*)(&app_regs.REG_DO3_CH),
	(uint8_t*)(&app_regs.REG_DO4_CH),
	(uint8_t*)(&app_regs.REG_DO5_CH),
	(uint8_t*)(&app_regs.REG_DO6_CH),
	(uint8_t*)(&app_regs.REG_DO7_CH),
	(uint8_t*)(&app_regs.REG_DO0_TH_VALUE),
	(uint8_t*)(&app_regs.REG_DO1_TH_VALUE),
	(uint8_t*)(&app_regs.REG_DO2_TH_VALUE),
	(uint8_t*)(&app_regs.REG_DO3_TH_VALUE),
	(uint8_t*)(&app_regs.REG_DO4_TH_VALUE),
	(uint8_t*)(&app_regs.REG_DO5_TH_VALUE),
	(uint8_t*)(&app_regs.REG_DO6_TH_VALUE),
	(uint8_t*)(&app_regs.REG_DO7_TH_VALUE),
	(uint8_t*)(&app_regs.REG_DO0_TH_UP_MS),
	(uint8_t*)(&app_regs.REG_DO1_TH_UP_MS),
	(uint8_t*)(&app_regs.REG_DO2_TH_UP_MS),
	(uint8_t*)(&app_regs.REG_DO3_TH_UP_MS),
	(uint8_t*)(&app_regs.REG_DO4_TH_UP_MS),
	(uint8_t*)(&app_regs.REG_DO5_TH_UP_MS),
	(uint8_t*)(&app_regs.REG_DO6_TH_UP_MS),
	(uint8_t*)(&app_regs.REG_DO7_TH_UP_MS),
	(uint8_t*)(&app_regs.REG_DO0_TH_DOWN_MS),
	(uint8_t*)(&app_regs.REG_DO1_TH_DOWN_MS),
	(uint8_t*)(&app_regs.REG_DO2_TH_DOWN_MS),
	(uint8_t*)(&app_regs.REG_DO3_TH_DOWN_MS),
	(uint8_t*)(&app_regs.REG_DO4_TH_DOWN_MS),
	(uint8_t*)(&app_regs.REG_DO5_TH_DOWN_MS),
	(uint8_t*)(&app_regs.REG_DO6_TH_DOWN_MS),
	(uint8_t*)(&app_regs.REG_DO7_TH_DOWN_MS),
	(uint8_t*)(&app_regs.REG_EVNT_ENABLE)
};

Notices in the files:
parts and their libraries:
SparkFun-Connectors: Licensing: Creative Commons ShareAlike 4.0 International - https://creativecommons.org/licenses/by-sa/4.0
